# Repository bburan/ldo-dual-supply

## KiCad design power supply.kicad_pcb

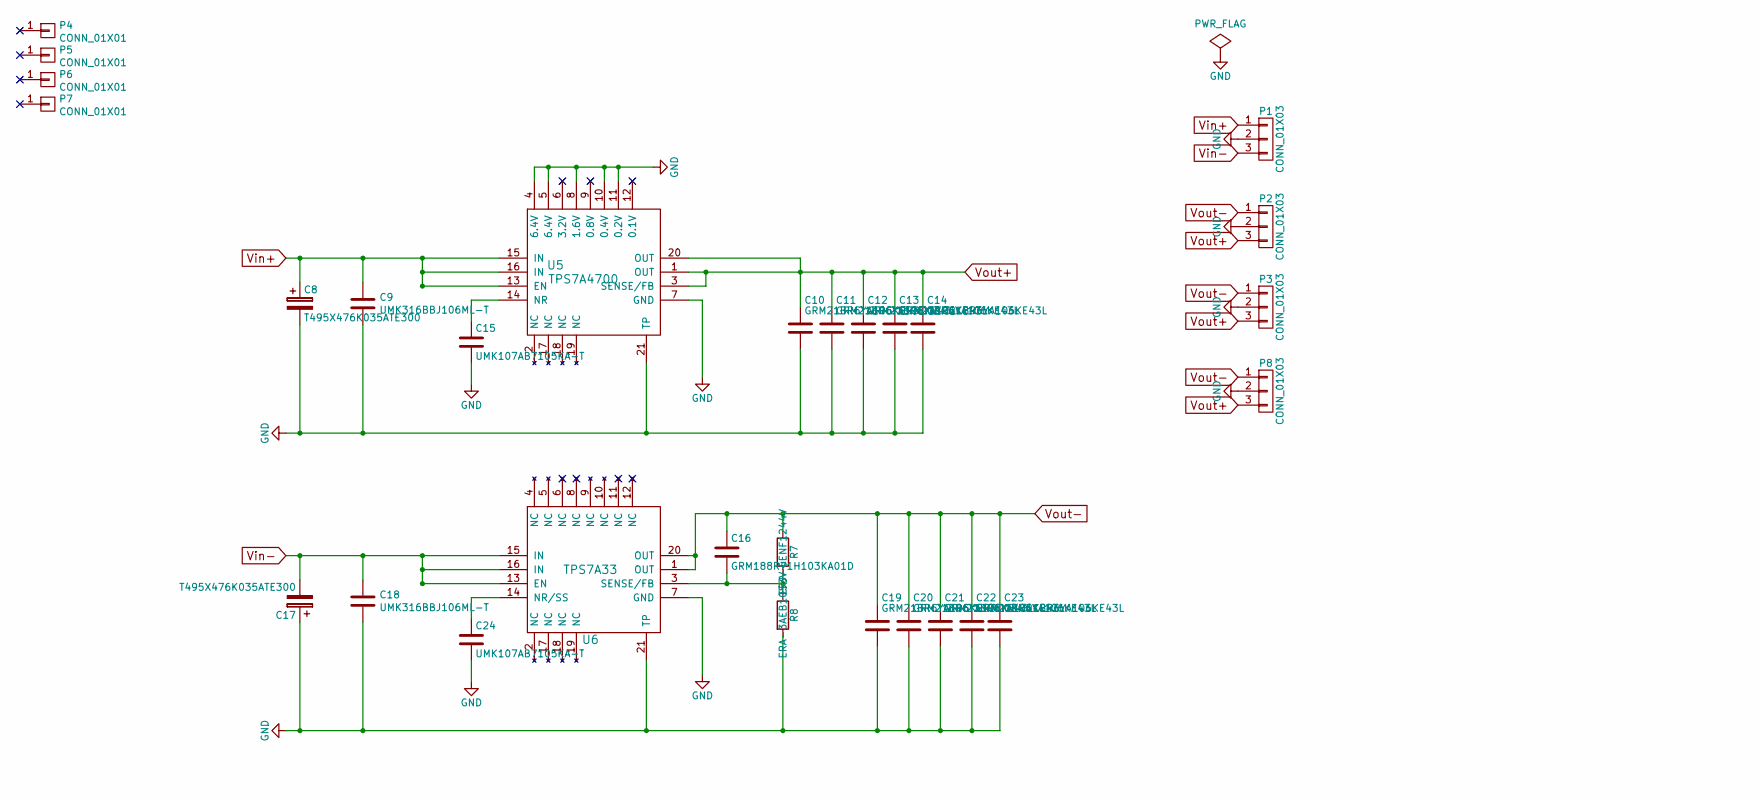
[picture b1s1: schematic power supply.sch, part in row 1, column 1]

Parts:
C8, C17: T495X476K035ATE300; TantalC_SizeD_EIA-7343_Reflow
C9, C18: UMK316BBJ106ML-T; C_1206
C10, C11, C12, C13, C14, C19, C20, C21, C22, C23: GRM21BR6YA106KE43L; C_0805
C15, C24: UMK107AB7105KA-T; C_0603
C16: GRM188R71H103KA01D; C_0603
P1, P2, P3, P8: CONN_01X03; Socket_Strip_Straight_1x03
P4, P5, P6, P7: CONN_01X01; 1pin
R7: ERJ-6ENF1244V; R_0805
R8: ERA-3AEB1053V; R_0603
U5: TPS7A4700; QFN-20-1EP_5x5mm_Pitch0.65mm
U6: TPS7A33; QFN-20-1EP_5x5mm_Pitch0.65mm

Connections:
GND: C8.2, C9.2, C10.2, C11.2, C12.2, C13.2, C14.2, C15.2, C17.1, C18.2, C19.2, C20.2, C21.2, C22.2, C23.2, C24.2, P1.2, P2.2, P3.2, P8.2, R8.2, U5.4 (6.4V), U5.5 (6.4V), U5.7 (GND), U5.8 (1.6V), U5.10 (0.4V), U5.11 (0.2V), U5.21 (TP), U6.7 (GND), U6.21 (TP)
unnamed: C15.1, U5.14 (NR)
unnamed: C16.2, R7.2, R8.1, U6.3 (SENSE/FB)
unnamed: C24.1, U6.14 (NR/SS)
Vin+: C8.1, C9.1, P1.1, U5.13 (EN), U5.15 (IN), U5.16 (IN)
Vin-: C17.2, C18.1, P1.3, U6.13 (EN), U6.15 (IN), U6.16 (IN)
Vout+: C10.1, C11.1, C12.1, C13.1, C14.1, P2.3, P3.3, P8.3, U5.1 (OUT), U5.3 (SENSE/FB), U5.20 (OUT)
Vout-: C16.1, C19.1, C20.1, C21.1, C22.1, C23.1, P2.1, P3.1, P8.1, R7.1, U6.1 (OUT), U6.20 (OUT)

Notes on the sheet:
10 uF capacitor - C1210C106K5RACTU (Kemet) 47 uF capacitor - UCZ1J470MCL6GS (Nichion) 1 uF capacitor - C1210C105K1RACTU (Kemet) 47 uF capacitor (output) - C2220C476M3R2CTU (Kemet) 10 nF capacitor - C0402C103K3RACTU (Kemet) 10.2 kOhm resistor - TNPW040210K2BEED (Vishay) 76.8 kOhm resistor - TNPW0402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
http://www.ti.com/lit/df/tidrgc7/tidrgc7.pdf http://www.ti.com/tool/PMP10651#2 http://www.ti.com/lit/ug/tidu855/tidu855.pdf http://www.ti.com/tool/TIDA-00401 http://www.ti.com/product/TPS7A30/toolssoftware http://www.mouser.com/Power/Power-Supplies/Plug-In-AC-Adapters/_/N-brvy9?P=1yx5k7vZ1yxt63yZ1y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

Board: 2 copper layers, 29 parts (12 on the bottom side), 8 nets, no tracks yet.

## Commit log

2016-05-30 Initial working schematic and PCB layout
